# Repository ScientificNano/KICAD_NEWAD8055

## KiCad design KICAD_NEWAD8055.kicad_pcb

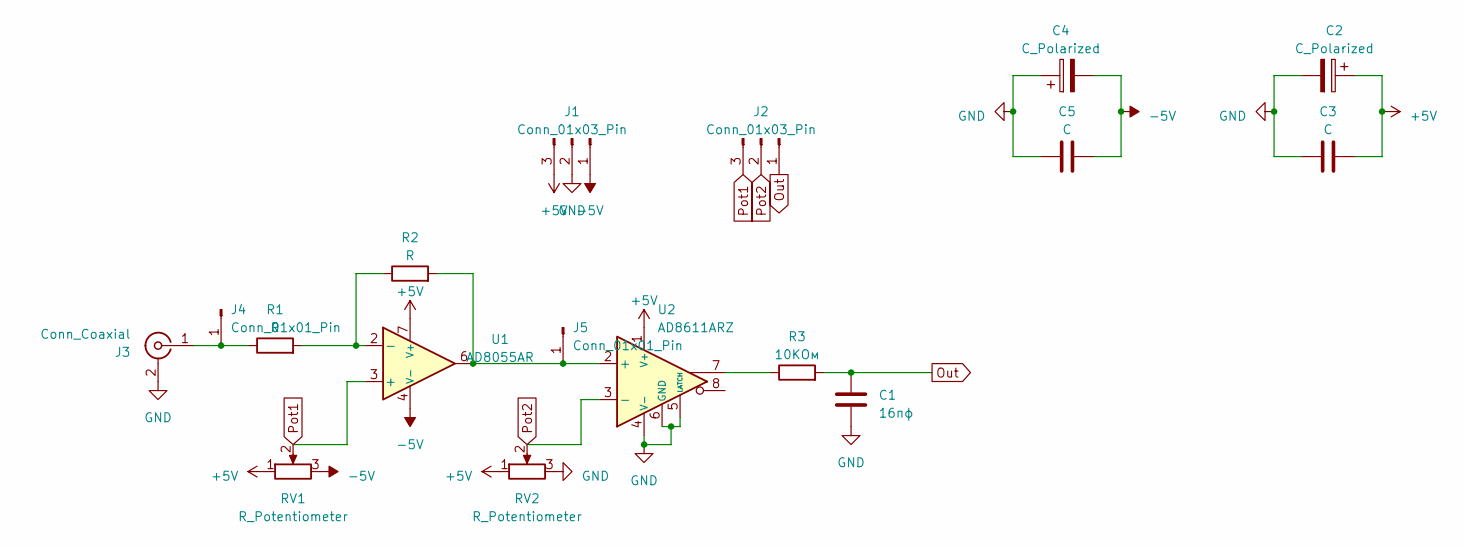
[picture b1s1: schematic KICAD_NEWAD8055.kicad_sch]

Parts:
C1: 16пф; C_0805_2012Metric_Pad1.18x1.45mm_HandSolder
C2, C4: C_Polarized; CP_EIA-3216-18_Kemet-A_Pad1.58x1.35mm_HandSolder
C3, C5: C; C_0805_2012Metric_Pad1.18x1.45mm_HandSolder
J1, J2: Conn_01x03_Pin; PinHeader_1x03_P2.54mm_Vertical
J3: Conn_Coaxial; U.FL_Hirose_U.FL-R-SMT-1_Vertical
J4, J5: Conn_01x01_Pin; PinHeader_1x01_P2.54mm_Vertical
R1, R2: R; R_1206_3216Metric_Pad1.30x1.75mm_HandSolder
R3: 10KОм; R_1206_3216Metric_Pad1.30x1.75mm_HandSolder
RV1, RV2: R_Potentiometer; Potentiometer_Bourns_3296W_Vertical
U1: AD8055AR; SO-8_3.9x4.9mm_P1.27mm
U2: AD8611ARZ; SO-8_3.9x4.9mm_P1.27mm

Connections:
+5V: C2.1, C3.2, J1.3, RV1.1, RV2.1, U1.7 (V+), U2.1 (V+)
-5V: C4.2, C5.2, J1.1, RV1.3, U1.4 (V-)
GND: C1.2, C2.2, C3.1, C4.1, C5.1, J1.2, J3.2 (Ext), RV2.3, U2.4 (V-), U2.5 (LATCH), U2.6 (GND)
unnamed: J3.1 (In), J4.1, R1.1
unnamed: J5.1, R2.2, U1.6, U2.2 (+)
unnamed: R3.1, U2.7
unnamed: R1.2, R2.1, U1.2 (-)
Out: C1.1, J2.1, R3.2
Pot1: J2.3, RV1.2, U1.3 (+)
Pot2: J2.2, RV2.2, U2.3 (-)

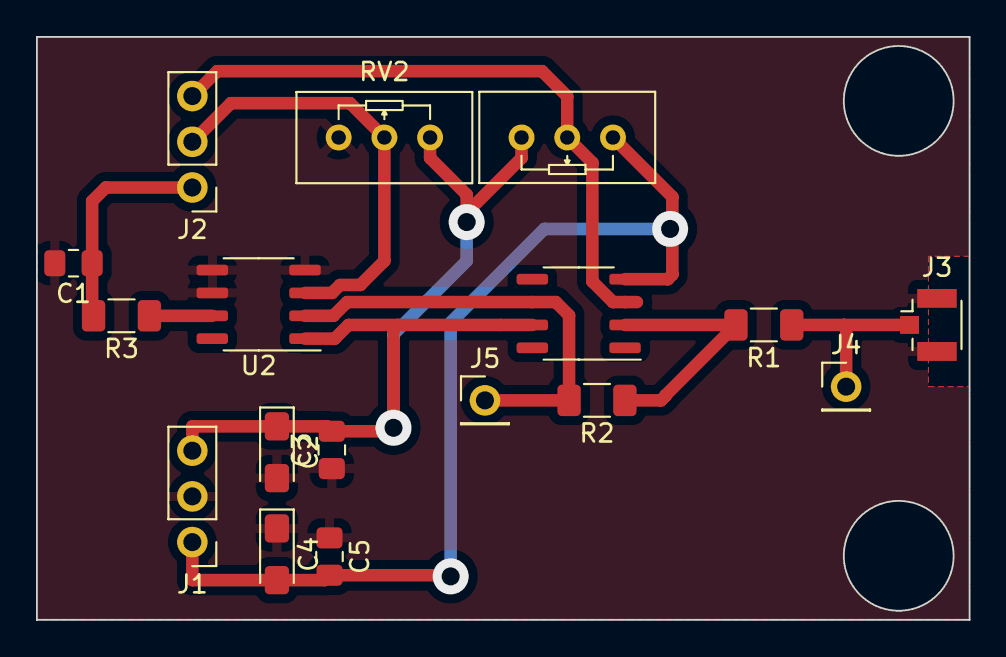
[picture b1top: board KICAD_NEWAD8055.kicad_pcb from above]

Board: 2 copper layers, 51.8 x 32.4 mm, 17 parts (0 on the bottom side), 10 nets.

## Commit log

2023-11-22 New pcb board and schematic
